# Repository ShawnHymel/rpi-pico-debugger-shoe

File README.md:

# RPi Pico Debugger Shoe

Stackable debugger board for the Raspberry Pi Pico. Solder long headers to this debugger board in order to connect the Pico to it. You will also need to connect jumper wires from the bottom CLK, GND, DIO pins to the target pico.

All design files were created using KiCad v5.1.

Feel free to modify this design for your own applciation. This PCB is intended to be a project for testing the layout of the Raspberry Pi RP2040.

Recommended reading:
 * [RP2040 Datasheet](https://datasheets.raspberrypi.org/rp2040/rp2040-datasheet.pdf)
 * [Hardware design with RP2040](https://datasheets.raspberrypi.org/rp2040/hardware-design-with-rp2040.pdf)

## License

Schematic and PCB layout files are licensed under the [CC BY 4.0](https://creativecommons.org/licenses/by/2.0/) license.

THE DESIGN IS PROVIDED "AS IS" AND THE AUTHOR DISCLAIMS ALL WARRANTIES WITH REGARD TO THIS DESIGN INCLUDING ALL IMPLIED WARRANTIES OF MERCHANTABILITY AND FITNESS. IN NO EVENT SHALL THE AUTHOR BE LIABLE FOR ANY SPECIAL, DIRECT, INDIRECT, OR CONSEQUENTIAL DAMAGES OR ANY DAMAGES WHATSOEVER RESULTING FROM LOSS OF USE, DATA OR PROFITS, WHETHER IN AN ACTION OF CONTRACT, NEGLIGENCE OR OTHER TORTIOUS ACTION, ARISING OUT OF OR IN CONNECTION WITH THE USE OR PERFORMANCE OF THIS DESIGN.

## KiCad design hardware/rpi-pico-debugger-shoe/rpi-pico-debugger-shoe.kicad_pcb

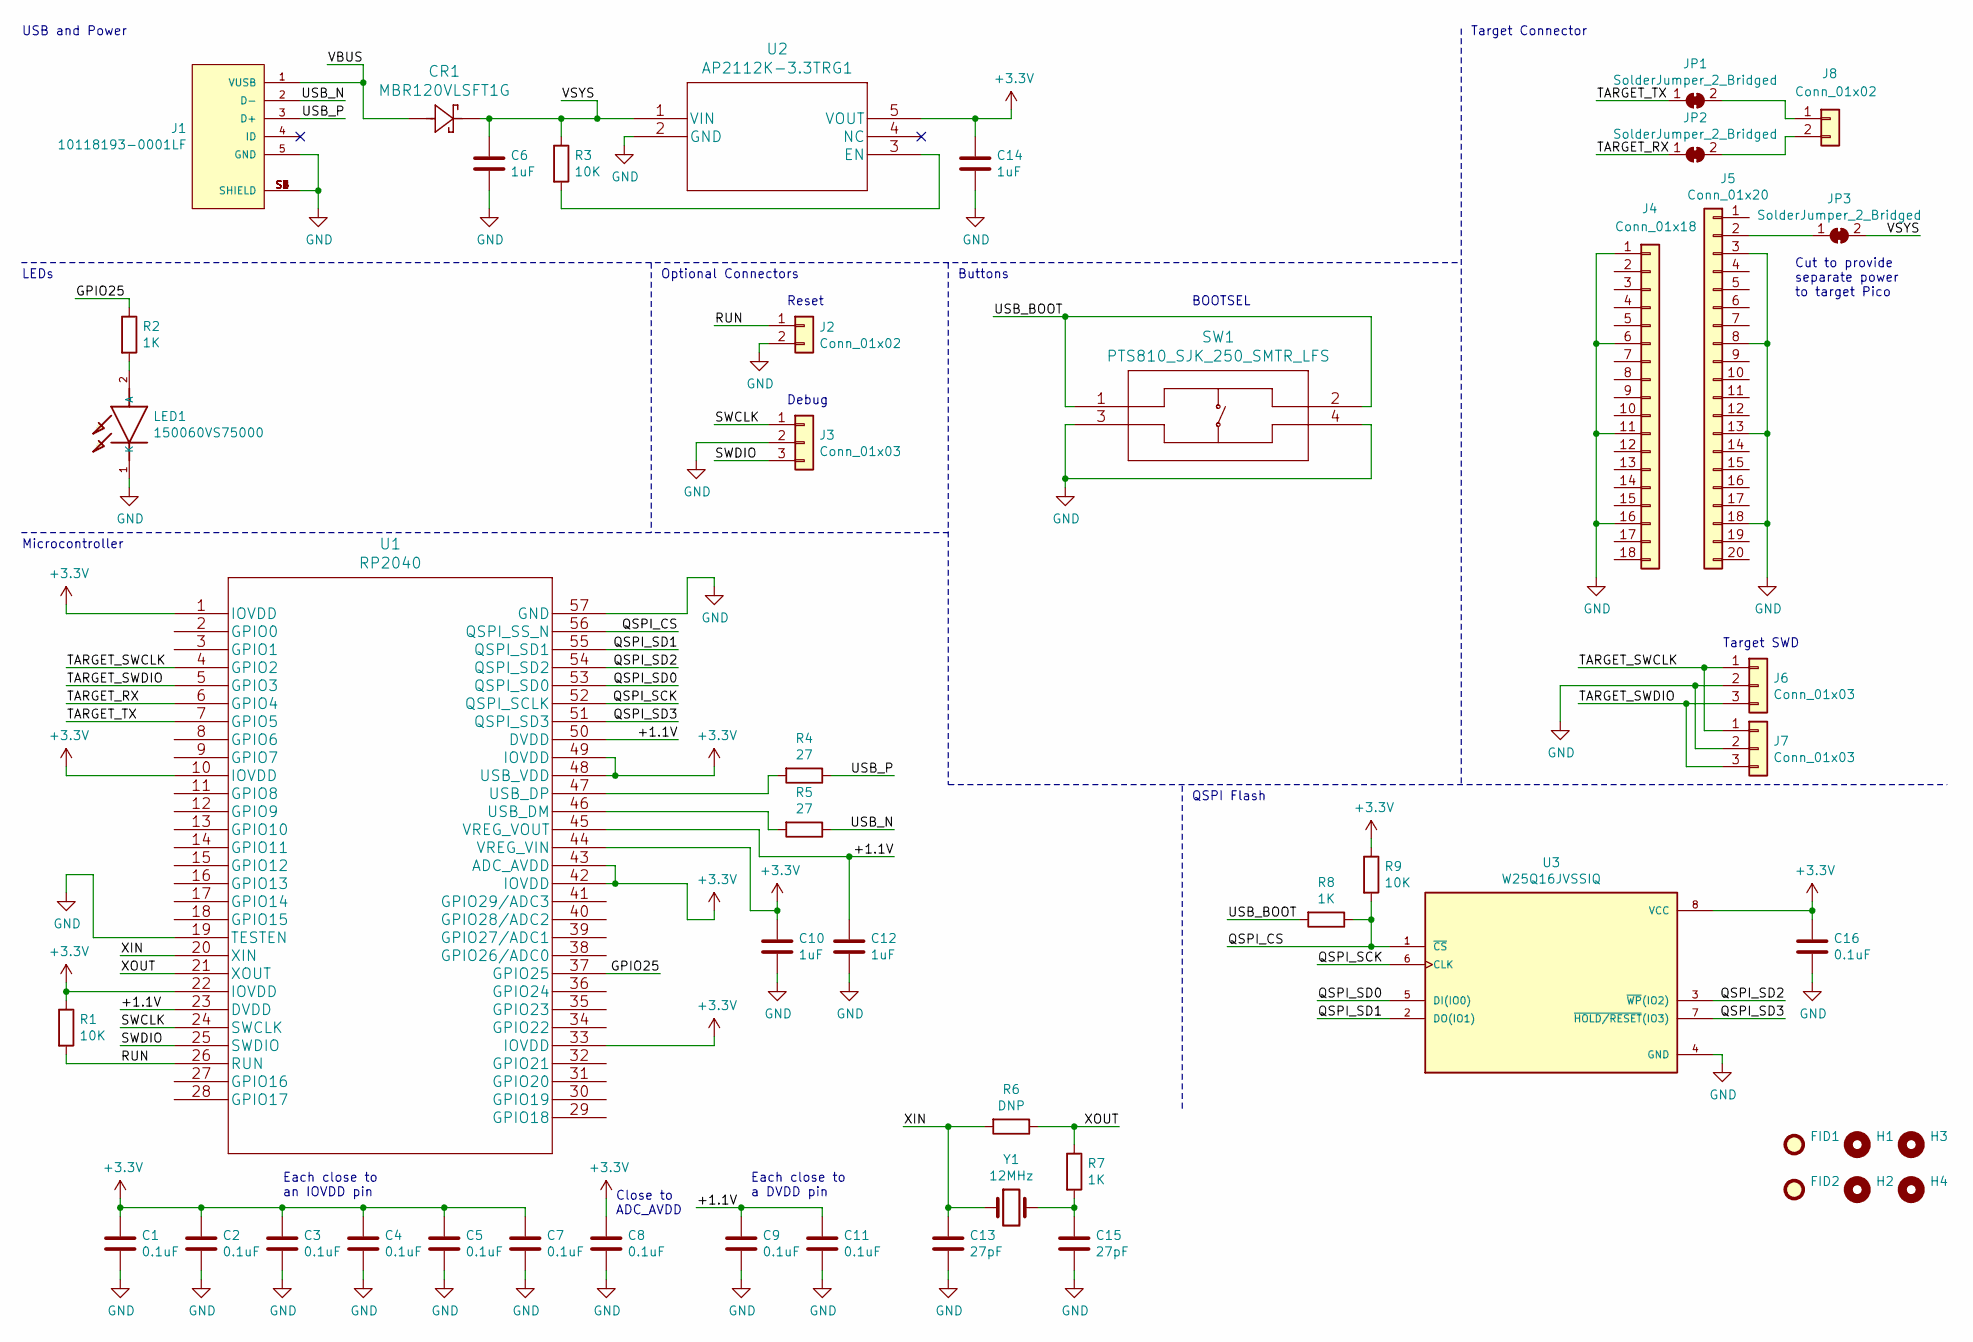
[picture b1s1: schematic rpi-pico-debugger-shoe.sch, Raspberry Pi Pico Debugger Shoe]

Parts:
C1, C2, C3, C4, C5, C7, C8, C9, C11, C16: 0.1uF; C_0603_1608Metric_Pad1.08x0.95mm_HandSolder; Digi-Key_PN 311-1344-1-ND
C6, C10, C12, C14: 1uF; C_0603_1608Metric_Pad1.08x0.95mm_HandSolder; Digi-Key_PN 1276-6524-1-ND
C13, C15: 27pF; C_0603_1608Metric_Pad1.08x0.95mm_HandSolder; Digi-Key_PN 311-1063-1-ND
CR1: MBR120VLSFT1G; Digi-Key_PN MBR120VLSFT1GOSCT-ND
FID1, FID2: Fiducial; Fiducial_1mm_Mask2mm
H1, H2, H3, H4: MountingHole; MountingHole_2.1mm
J1: 10118193-0001LF; FCI_10118193-0001LF_no-slot; Digi-Key_PN 609-4616-1-ND
J2: Conn_01x02; PinHeader_1x02_P2.54mm_Vertical_no-silk
J3, J6: Conn_01x03; PinHeader_1x03_P2.54mm_Vertical_no-silk
J4: Conn_01x18; PinHeader_1x18_P2.54mm_Vertical_no-silk; Digi-Key_PN 1988-1035-ND
J5: Conn_01x20; PinHeader_1x20_P2.54mm_Vertical_no-silk; Digi-Key_PN 1988-1136-ND
J7: Conn_01x03; PinHeader_1x03_P2.54mm_Vertical_no-silk; Digi-Key_PN S7036-ND
J8: Conn_01x02; PinHeader_1x02_P2.54mm_Vertical_no-silk; Digi-Key_PN S7035-ND
JP1, JP2, JP3: SolderJumper_2_Bridged; SolderJumper-2_P1.3mm_Bridged_RoundedPad1.0x1.5mm
LED1: 150060VS75000; LEDC1608X80N; MOUSER_PART_NUMBER 710-150060VS75000
R1, R3, R9: 10K; R_0603_1608Metric_Pad0.98x0.95mm_HandSolder; Digi-Key_PN 311-10KGRCT-ND
R2, R7, R8: 1K; R_0603_1608Metric_Pad0.98x0.95mm_HandSolder; Digi-Key_PN 311-1.00KHRCT-ND
R4, R5: 27; R_0603_1608Metric_Pad0.98x0.95mm_HandSolder; Digi-Key_PN 311-27.0HRCT-ND
R6: DNP; R_0603_1608Metric_Pad0.98x0.95mm_HandSolder
SW1: PTS810_SJK_250_SMTR_LFS; PTS810 SJK 250 SMTR LFS; Digi-Key_PN CKN10503CT-ND
U1: RP2040; Digi-Key_PN TBD
U2: AP2112K-3.3TRG1; Digi-Key_PN AP2112K-3.3TRG1DICT-ND
U3: W25Q16JVSSIQ; SOIC127P790X216-8N; Digi-Key_PN 256-W25Q16JVSSIM-ND
Y1: 12MHz; ABLS7M2-16.000MHZ-D-2Y-T; Digi-Key_PN 535-13415-1-ND

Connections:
+3V3: C1.1, C2.1, C3.1, C4.1, C5.1, C7.1, C8.1, C10.1, C14.1, C16.1, R1.1, R9.1, U1.1 (IOVDD), U1.10 (IOVDD), U1.22 (IOVDD), U1.33 (IOVDD), U1.42 (IOVDD), U1.43 (ADC_AVDD), U1.44 (VREG_VIN), U1.48 (USB_VDD), U1.49 (IOVDD), U2.5 (VOUT), U3.8 (VCC)
/+1.1V: C9.1, C11.1, C12.1, U1.23 (DVDD), U1.45 (VREG_VOUT), U1.50 (DVDD)
/GPIO25: R2.1, U1.37 (GPIO25)
/QSPI_CS: R8.1, R9.2, U1.56 (QSPI_SS_N), U3.1 (~CS)
/QSPI_SCK: U1.52 (QSPI_SCLK), U3.6 (CLK)
/QSPI_SD0: U1.53 (QSPI_SD0), U3.5 (DI(IO0))
/QSPI_SD1: U1.55 (QSPI_SD1), U3.2 (DO(IO1))
/QSPI_SD2: U1.54 (QSPI_SD2), U3.3 (~WP~(IO2))
/QSPI_SD3: U1.51 (QSPI_SD3), U3.7 (~HOLD/RESET~(IO3))
/RUN: J2.1, R1.2, U1.26 (RUN)
/SWCLK: J3.1, U1.24 (SWCLK)
/SWDIO: J3.3, U1.25 (SWDIO)
/TARGET_RX: JP2.1 (A), U1.6 (GPIO4)
/TARGET_SWCLK: J6.1, J7.1, U1.4 (GPIO2)
/TARGET_SWDIO: J6.3, J7.3, U1.5 (GPIO3)
/TARGET_TX: JP1.1 (A), U1.7 (GPIO5)
/USB_BOOT: R8.2, SW1.1, SW1.2
/USB_N: J1.2 (D-), R5.1
/USB_P: J1.3 (D+), R4.1
/VBUS: CR1.2, J1.1 (VUSB)
/VSYS: C6.1, CR1.1, JP3.2 (B), R3.1, U2.1 (VIN)
/XIN: C13.1, R6.2, U1.20 (XIN), Y1.1
/XOUT: R6.1, R7.1, U1.21 (XOUT)
GND: C1.2, C2.2, C3.2, C4.2, C5.2, C6.2, C7.2, C8.2, C9.2, C10.2, C11.2, C12.2, C13.2, C14.2, C15.2, C16.2, J1.5 (GND), J1.S1 (SHIELD), J1.S2 (SHIELD), J1.S3 (SHIELD), J1.S4 (SHIELD), J1.S5 (SHIELD), J1.S6 (SHIELD), J2.2, J3.2, J4.1, J4.6, J4.11, J4.16, J5.3, J5.8, J5.13, J5.18, J6.2, J7.2, LED1.1 (K), SW1.3, SW1.4, U1.19 (TESTEN), U1.57 (GND), U2.2 (GND), U3.4 (GND)
unnamed: C15.1, R7.2, Y1.2
unnamed: J5.2, JP3.1 (A)
unnamed: J8.1, JP1.2 (B)
unnamed: J8.2, JP2.2 (B)
unnamed: LED1.2 (A), R2.2
unnamed: R3.2, U2.3 (EN)
unnamed: R4.2, U1.47 (USB_DP)
unnamed: R5.2, U1.46 (USB_DM)

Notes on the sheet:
Close to ADC_AVDD
Each close to an IOVDD pin
Each close to a DVDD pin
BOOTSEL
Debug
Reset
Target SWD
Buttons
USB and Power
LEDs
Optional Connectors
Target Connector
Microcontroller
QSPI Flash
Cut to provide separate power to target Pico

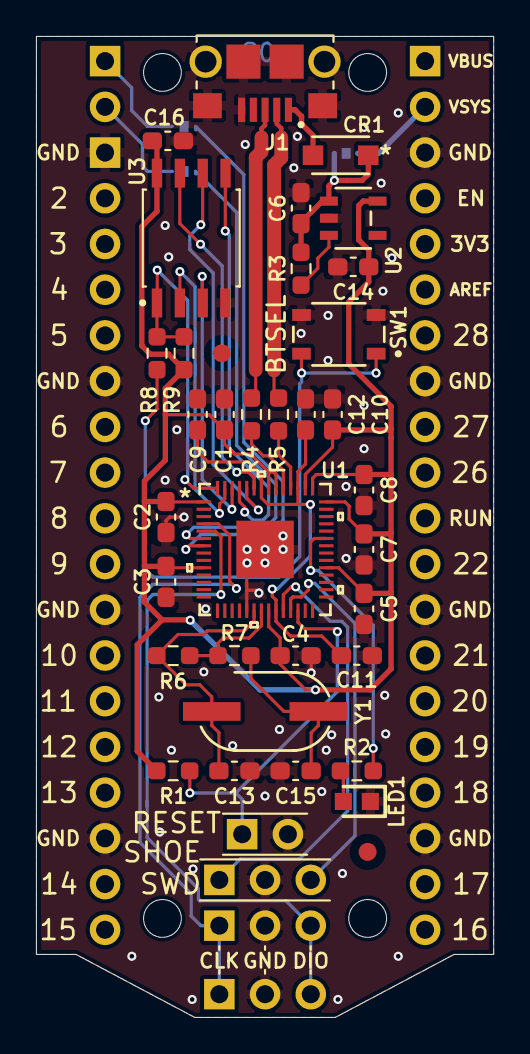
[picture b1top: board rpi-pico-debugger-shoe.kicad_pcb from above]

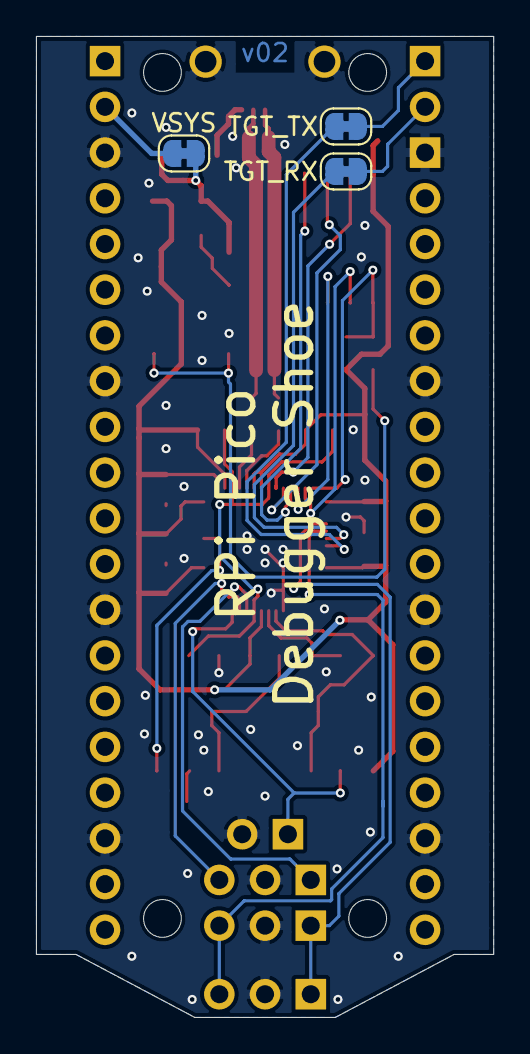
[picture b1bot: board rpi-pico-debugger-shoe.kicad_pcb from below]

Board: 2 copper layers, 25.4 x 54.5 mm, 49 parts (3 on the bottom side), 32 nets.

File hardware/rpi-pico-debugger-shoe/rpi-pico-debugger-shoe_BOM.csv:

Reference, Quantity, Value, Digi-Key_PN,Digi-Key_Substitute
C13 C15 ,2,27pF,311-1063-1-ND,
C6 C10 C12 C14 ,4,1uF,1276-6524-1-ND,
C1 C2 C3 C4 C5 C7 C8 C9 C11 C16 ,10,0.1uF,311-1344-1-ND,
CR1 ,1,MBR120VLSFT1G,MBR120VLSFT1GOSCT-ND,SM5817PL-TPMSCT-ND
J1 ,1,10118193-0001LF,609-4616-1-ND,
J2,1,Conn_01x02,,
J8,1,Conn_01x02,S7035-ND,
J3 J6,2,Conn_01x03,,
J7,1,Conn_01x03,S7036-ND,
J4 ,1,Conn_01x18,1988-1035-ND,
J5 ,1,Conn_01x20,1988-1136-ND,
JP1 JP2 JP3 ,3,SolderJumper_2_Bridged,,
LED1 ,1,150060VS75000,732-4980-1-ND,
R1 R3 R9 ,3,10K,311-10KGRCT-ND,
R4 R5 ,2,27,311-27.0HRCT-ND,
R6 ,1,DNP,,
R2 R7 R8 ,3,1K,311-1.00KHRCT-ND,
SW1 ,1,PTS810_SJK_250_SMTR_LFS,CKN10503CT-ND,
U1 ,1,RP2040,TBD,
U2 ,1,AP2112K-3.3TRG1,AP2112K-3.3TRG1DICT-ND,893-1075-1-ND
U3 ,1,W25Q16JVSSIQ,256-W25Q16JVSSIM-ND,1092-1222-ND
Y1 ,1,12MHz,535-13415-1-ND,

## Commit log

2021-05-12 Added some parts from third-party libraries
2021-05-14 Finished schematic and BOM for v01
2021-05-14 Added BOM file
2021-05-15 Did done some layouts
2021-05-16 Finished layout for v01
2021-05-18 Added image of shoe.
2021-05-19 Added PDF schematic
2021-06-05 Swapped R8 and R9 silk because I messed that up in v01.

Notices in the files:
hardware/rpi-pico-debugger-shoe/rpi-pico-debugger-shoe.kicad_pcb:
License: CC BY 4.0
hardware/rpi-pico-debugger-shoe/rpi-pico-debugger-shoe.sch:
https://creativecommons.org/licenses/by/4.0
parts and their libraries:
Copyright 2016 Accelerated Designs. All rights reserved.
